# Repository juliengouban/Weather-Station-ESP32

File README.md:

# Weather-Station-ESP32
In this board, I have designed a weather station based on the ESP32 with sensor of temperature, humidity and photoresistor. 
The ESP32 is a highly versatile and cost-effective microcontroller, ideal for PCB design due to its powerful dual-core processor, built-in Wi-Fi and Bluetooth, and low power consumption. Its wide range of I/O options and support for various communication protocols make it suitable for many applications, especially in IoT projects. The compact form factor and extensive development support further simplify the design process, allowing for efficient and flexible PCB layouts.

Our board is a two layers designed with Altium Designer.

<h1> Electronic diagram</h1>
We'll now take a closer look at how our electronic board works: 

For powering the circuit, we've used a Micro USB type B connector to supply our board with 5V. As the ESP32 uses 3.3V, we've fitted a regulator to convert 5V to +3.3V: 

We have added a clock module that allows for an accurate time even when our board is powered off. This module is powered by +5V and uses a coin cell battery when the board is off: 

We use a MicroSD card module to store temperature measurements along with a date and time, allowing us to generate graphs on our web server:

For the ESP32, we have chosen th ESP32-S3 Mini 1-N8. This is a compact and powerful microcontroller board designed by Espressif. It features the ESP32-S3 chip, which integrates a dual-core processor, Wi-Fi, and Bluetooth capabilities, making it ideal for a wide range of IoT applications. With 8MB of flash memory, this board offers ample storage for firmware and data. The ESP32-S3 Mini 1-N8 is known for its low power consumption, high performance, and rich set of peripherals, including SPI, I2C, UART, and GPIOs, making it a versatile solution for embedded systems and smart device development:

The DHT11 is a popular digital temperature and humidity sensor. It measures temperature from 0 to 50°C with ±2°C accuracy and humidity from 20 to 80% with ±5% accuracy. The sensor communicates via a single data pin, making it easy to integrate into projects like weather stations and environmental monitoring systems. It offers a good balance of cost and functionality for basic temperature and humidity measurements:

Finally we have added a photoresistor, which is a type of resistor whose resistance changes based on the amount of light it receives. In the presence of light, its resistance decreases, allowing more current to flow, while in darkness, its resistance increases, limiting the current:

<h1>PCB Design</h1>

The board is a 2-layer design. On the top you can see the 3.3V regulator and the Micro-USB type B connector.
In the middle of the board you'll find the ESP32 microcontroller and its wifi antenna.
At the right side of the board you will find the DHT11 sensor at the top, DS1307 module at the middle and at the bottom a MicroSD card.
A ground plane has been created on the TOP layer to connect all the GNDs together with a ground plane. This ground plane is around the wifi antenna but not to close to it.

Here are the 3d and top layer views of the PCB:

Here is a 3d view of the PCB:

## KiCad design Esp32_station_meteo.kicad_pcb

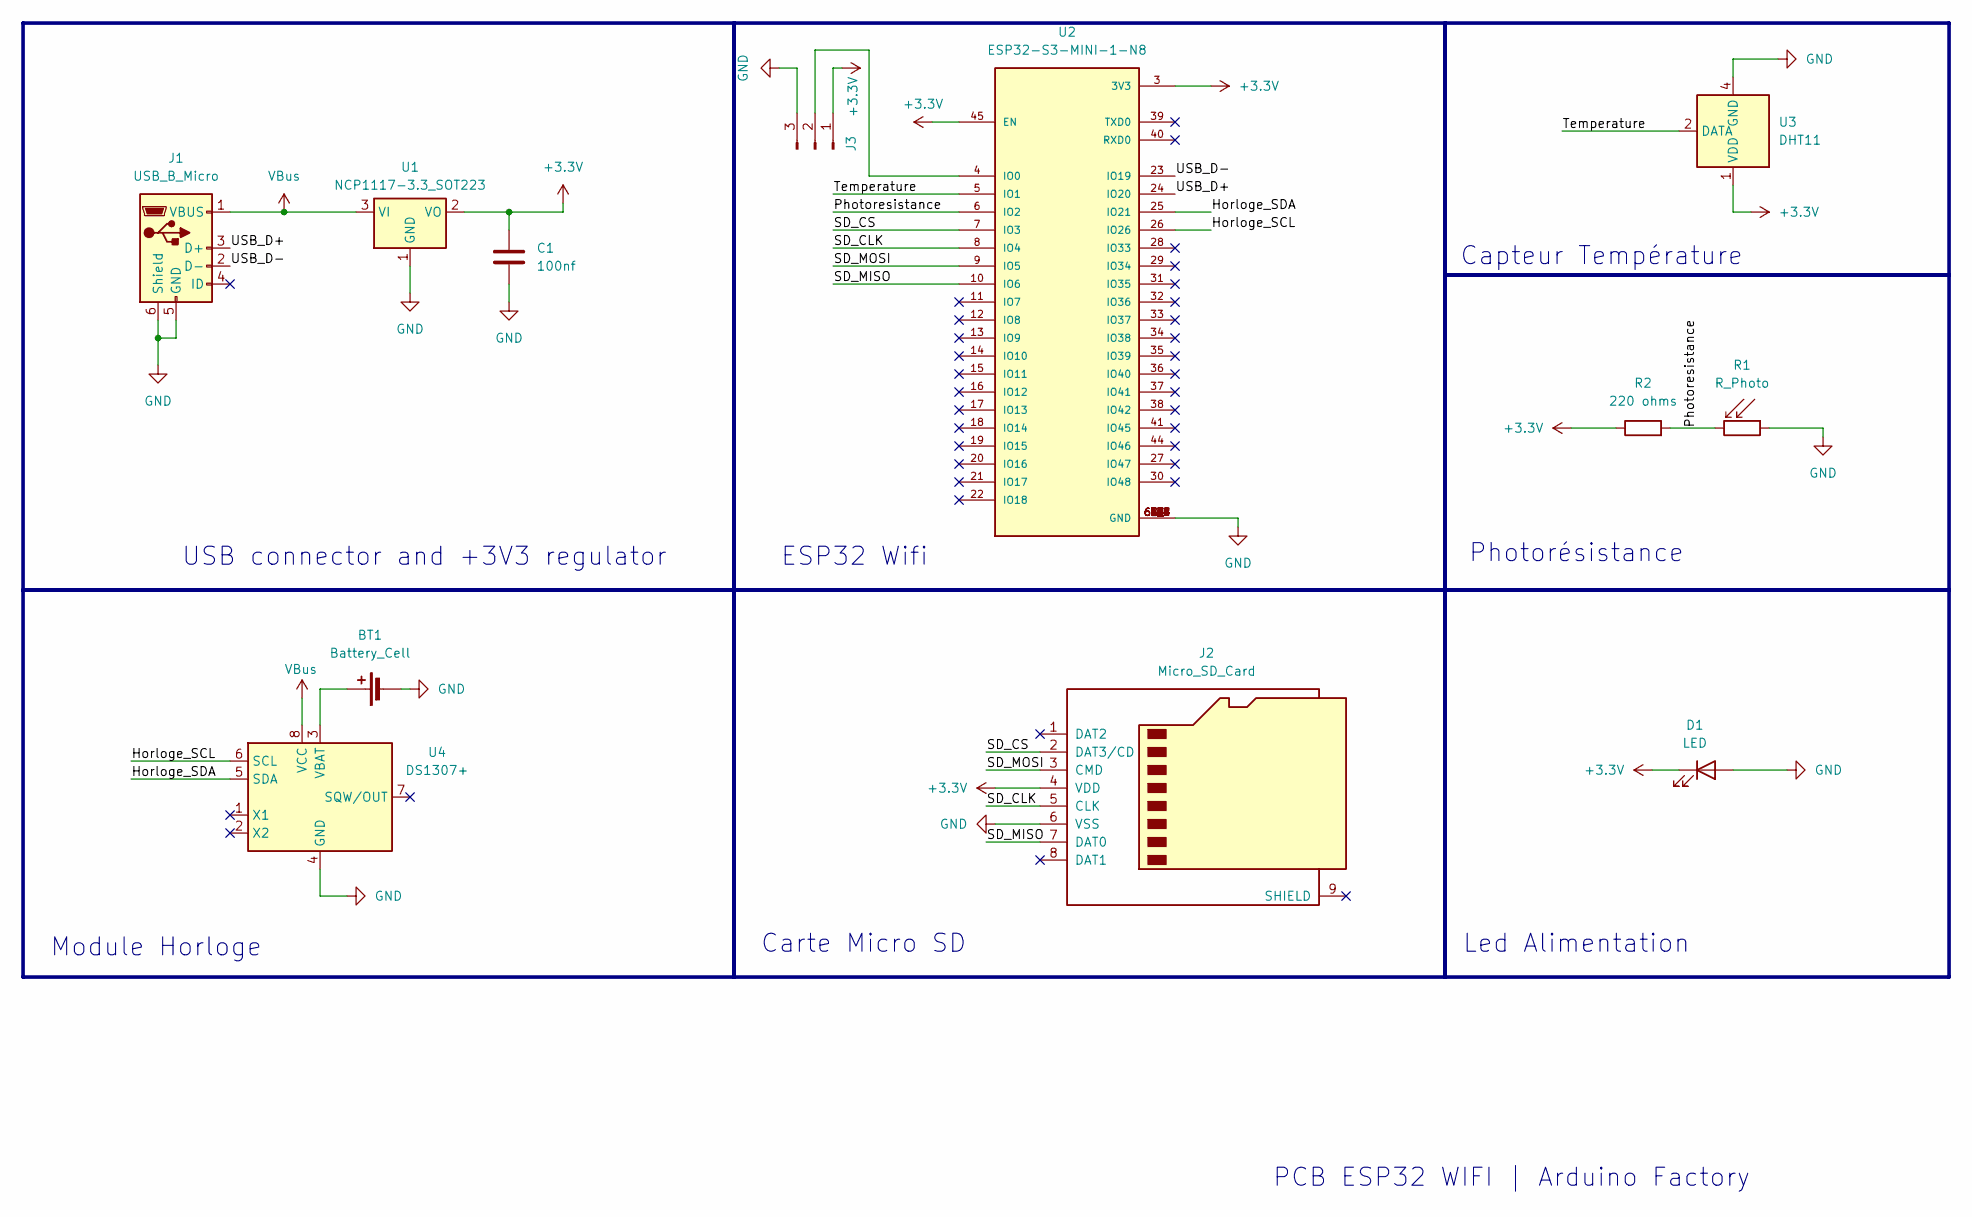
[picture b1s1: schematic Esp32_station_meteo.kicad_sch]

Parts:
BT1: Battery_Cell; Battery_Panasonic_CR1025-VSK_Vertical_CircularHoles
C1: 100nf; C_0402_1005Metric
D1: LED; LED_0402_1005Metric
J1: USB_B_Micro; USB_Micro-B_Amphenol_10103594-0001LF_Horizontal
J2: Micro_SD_Card; microSD_HC_Molex_47219-2001
J3: Conn_01x03_Pin; PinHeader_1x03_P1.27mm_Vertical
R1: R_Photo; PinHeader_2x01_P2.00mm_Vertical
R2: 220 ohms; R_0402_1005Metric
U1: NCP1117-3.3_SOT223; SOT-223-3_TabPin2
U2: ESP32-S3-MINI-1-N8; XCVR_ESP32-S3-MINI-1-N8; PARTREV v0.6
U3: DHT11; Aosong_DHT11_5.5x12.0_P2.54mm
U4: DS1307+; DIP-8_W7.62mm

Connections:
+3.3V: C1.1, D1.1 (K), J2.4 (VDD), J3.1, R2.1, U1.2 (VO), U2.3 (3V3), U2.45 (EN), U3.1 (VDD)
/Horloge_SCL: U2.26 (IO26), U4.6 (SCL)
/Horloge_SDA: U2.25 (IO21), U4.5 (SDA)
/Photoresistance: R1.2, R2.2, U2.6 (IO2)
/SD_CLK: J2.5 (CLK), U2.8 (IO4)
/SD_CS: J2.2 (DAT3/CD), U2.7 (IO3)
/SD_MISO: J2.7 (DAT0), U2.10 (IO6)
/SD_MOSI: J2.3 (CMD), U2.9 (IO5)
/Temperature: U2.5 (IO1), U3.2 (DATA)
/USB_D+: J1.3 (D+), U2.24 (IO20)
/USB_D-: J1.2 (D-), U2.23 (IO19)
GND: BT1.2 (-), C1.2, D1.2 (A), J1.5 (GND), J1.6 (Shield), J2.6 (VSS), J3.3, R1.1, U1.1 (GND), U2.1 (GND), U2.2 (GND), U2.42 (GND), U2.43 (GND), U2.46 (GND), U2.47 (GND), U2.48 (GND), U2.49 (GND), U2.50 (GND), U2.51 (GND), U2.52 (GND), U2.53 (GND), U2.54 (GND), U2.55 (GND), U2.56 (GND), U2.57 (GND), U2.58 (GND), U2.59 (GND), U2.60 (GND), U2.61 (GND), U2.61_1 (GND), U2.61_2 (GND), U2.61_3 (GND), U2.61_4 (GND), U2.61_5 (GND), U2.61_6 (GND), U2.61_7 (GND), U2.61_8 (GND), U2.62 (GND), U2.63 (GND), U2.64 (GND), U2.65 (GND), U3.4 (GND), U4.4 (GND)
unnamed: BT1.1 (+), U4.3 (VBAT)
unnamed: J3.2, U2.4 (IO0)
VBus: J1.1 (VBUS), U1.3 (VI), U4.8 (VCC)

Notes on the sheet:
Capteur Température
Module Horloge
Photorésistance
USB connector and +3V3 regulator
Carte Micro SD
Led Alimentation
ESP32 Wifi
PCB ESP32 WIFI | Arduino Factory

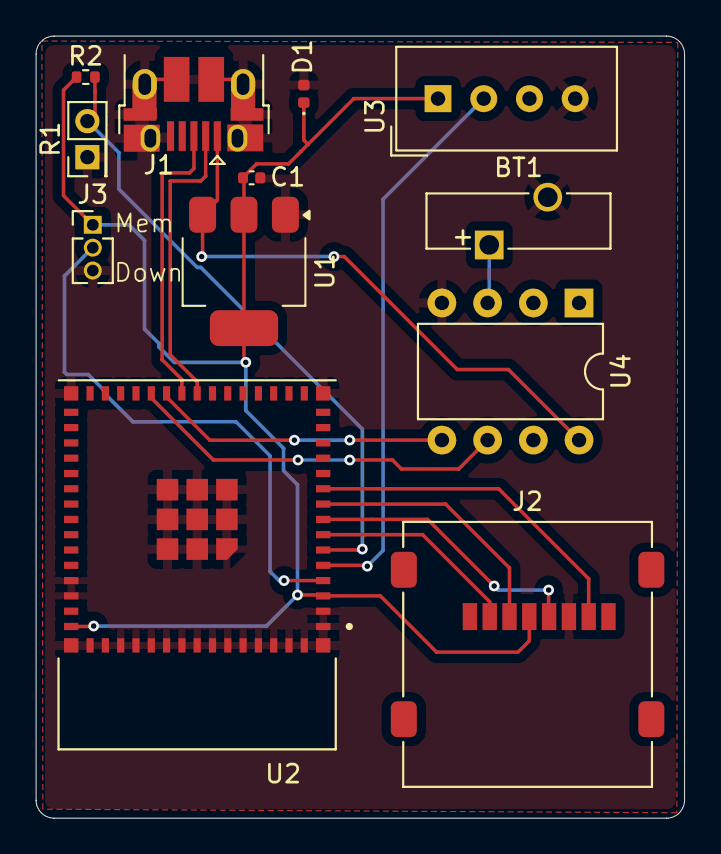
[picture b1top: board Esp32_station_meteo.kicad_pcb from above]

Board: 2 copper layers, 36.0 x 43.4 mm, 12 parts (0 on the bottom side), 15 nets.

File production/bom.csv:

Designator,Footprint,Quantity,Value,LCSC Part #
BT1,Battery_Panasonic_CR1025-VSK_Vertical_CircularHoles,1,Battery_Cell,
C1,0402,1,100nf,
D1,0402,1,LED,
J1,USB_Micro-B_Amphenol_10103594-0001LF_Horizontal,1,USB_B_Micro,
J2,microSD_HC_Molex_47219-2001,1,Micro_SD_Card,
J3,PinHeader_1x03_P1.27mm_Vertical,1,Conn_01x03_Pin,
R1,PinHeader_2x01_P2.00mm_Vertical,1,R_Photo,
R2,0402,1,220 ohms,
U1,SOT-223-3_TabPin2,1,NCP1117-3.3_SOT223,
U2,XCVR_ESP32-S3-MINI-1-N8,1,ESP32-S3-MINI-1-N8,
U3,Aosong_DHT11_5.5x12.0_P2.54mm,1,DHT11,
U4,DIP-8_W7.62mm,1,DS1307+,
